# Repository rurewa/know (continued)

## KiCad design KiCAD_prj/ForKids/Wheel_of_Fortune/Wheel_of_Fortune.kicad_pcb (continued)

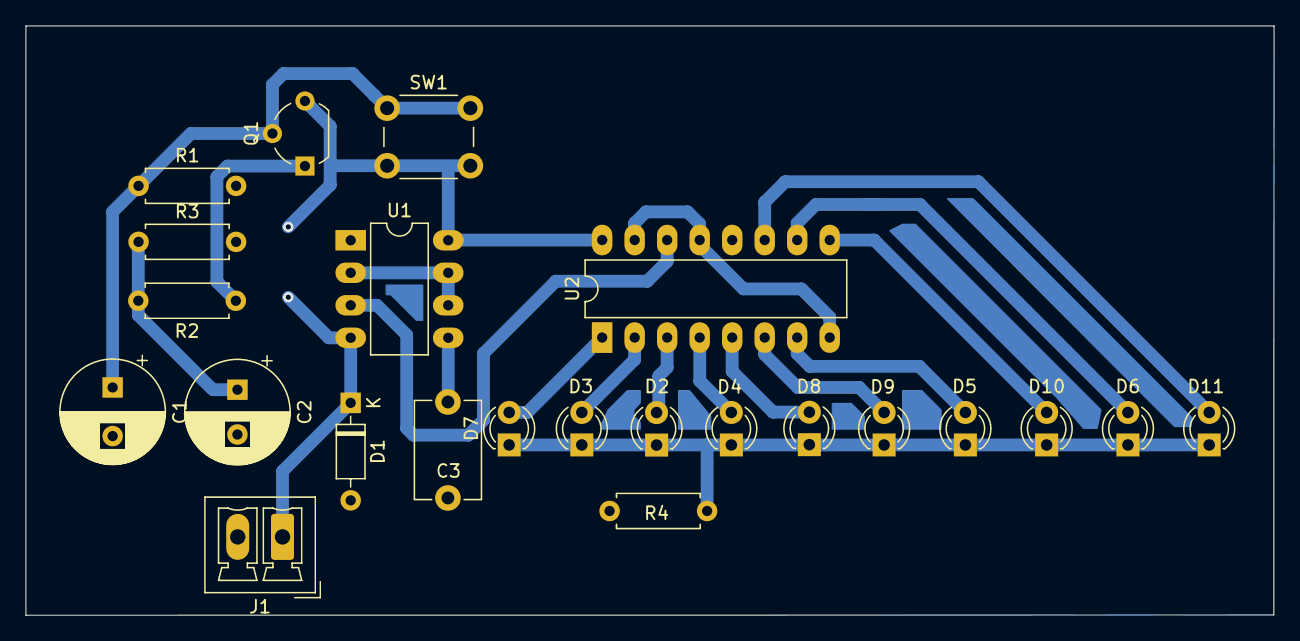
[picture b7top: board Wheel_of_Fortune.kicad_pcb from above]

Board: 2 copper layers, 97.5 x 46.0 mm, 23 parts (0 on the bottom side), 19 nets.

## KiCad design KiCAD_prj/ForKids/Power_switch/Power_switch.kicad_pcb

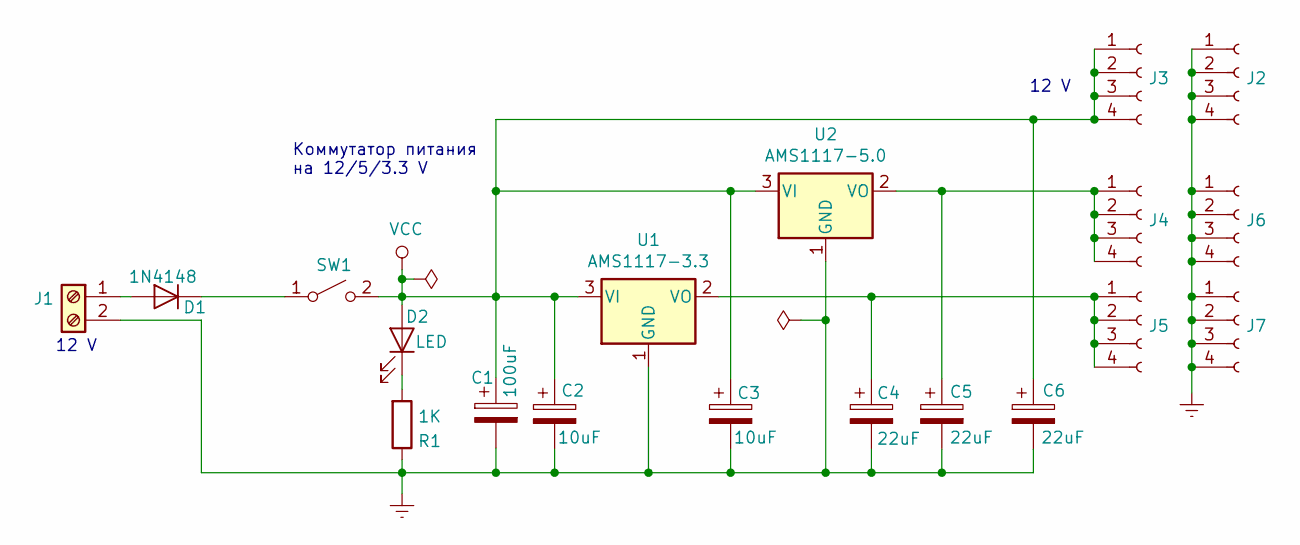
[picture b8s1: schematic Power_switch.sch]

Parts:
C1: 100uF; CP_Radial_D8.0mm_P5.00mm
C2, C3: 10uF; CP_Radial_D5.0mm_P2.50mm
C4, C5, C6: 22uF; CP_Radial_D5.0mm_P2.50mm
D1: 1N4148; D_DO-35_SOD27_P7.62mm_Horizontal
D2: LED; LED_D3.0mm
J1: Screw_Terminal_01x02; PhoenixContact_MCV_1,5_2-G-3.5_1x02_P3.50mm_Vertical
J2, J3, J4, J5, J6, J7: Conn_01x04_Female; PinHeader_1x04_P2.54mm_Vertical
R1: 1K; R_Axial_DIN0207_L6.3mm_D2.5mm_P7.62mm_Horizontal
SW1: SW_SPST; Nidec_Copal_SH-7010C
U1: AMS1117-3.3; SOT-223-3_TabPin2
U2: AMS1117-5.0; SOT-223-3_TabPin2

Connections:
Earth: C1.2, C2.2, C3.2, C4.2, C5.2, C6.2, J1.2, J2.1, J2.2, J2.3, J2.4, J6.1, J6.2, J6.3, J6.4, J7.1, J7.2, J7.3, J7.4, R1.1, U1.1 (GND), U2.1 (GND)
unnamed: C4.1, J5.1, J5.2, J5.3, J5.4, U1.2 (VO)
unnamed: C5.1, J4.1, J4.2, J4.3, J4.4, U2.2 (VO)
unnamed: D1.1 (K), SW1.1 (A)
unnamed: D1.2 (A), J1.1
unnamed: D2.1 (K), R1.2
VCC: C1.1, C2.1, C3.1, C6.1, D2.2 (A), J3.1, J3.2, J3.3, J3.4, SW1.2 (B), U1.3 (VI), U2.3 (VI)

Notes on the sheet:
12 V
Коммутатор питания на 12/5/3.3 V

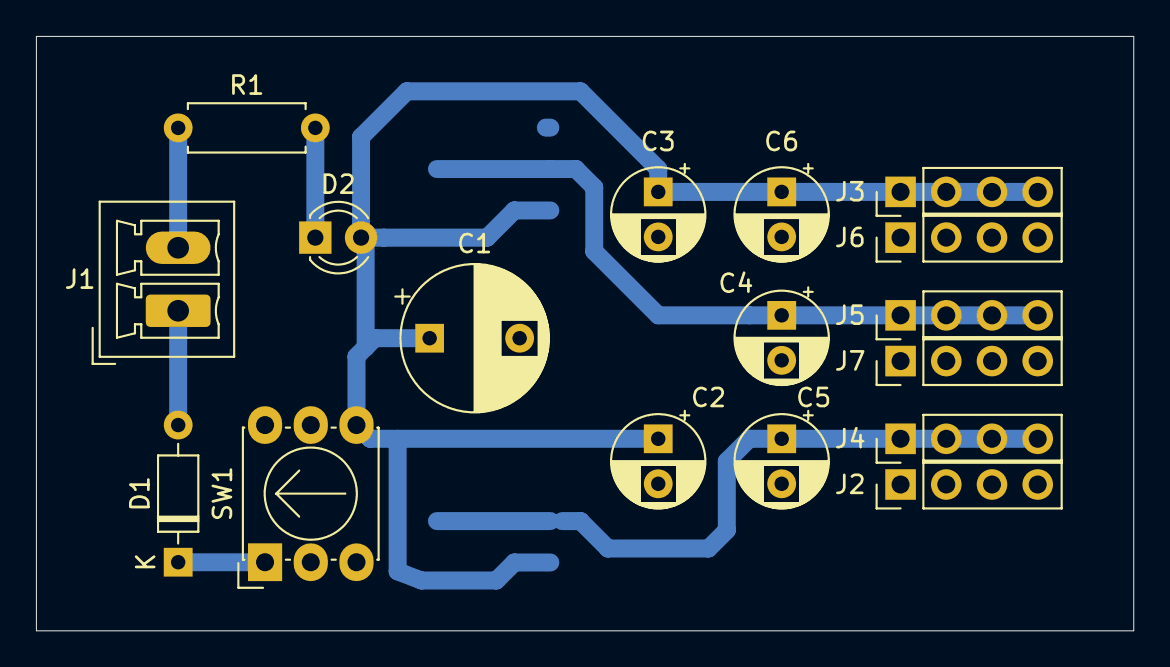
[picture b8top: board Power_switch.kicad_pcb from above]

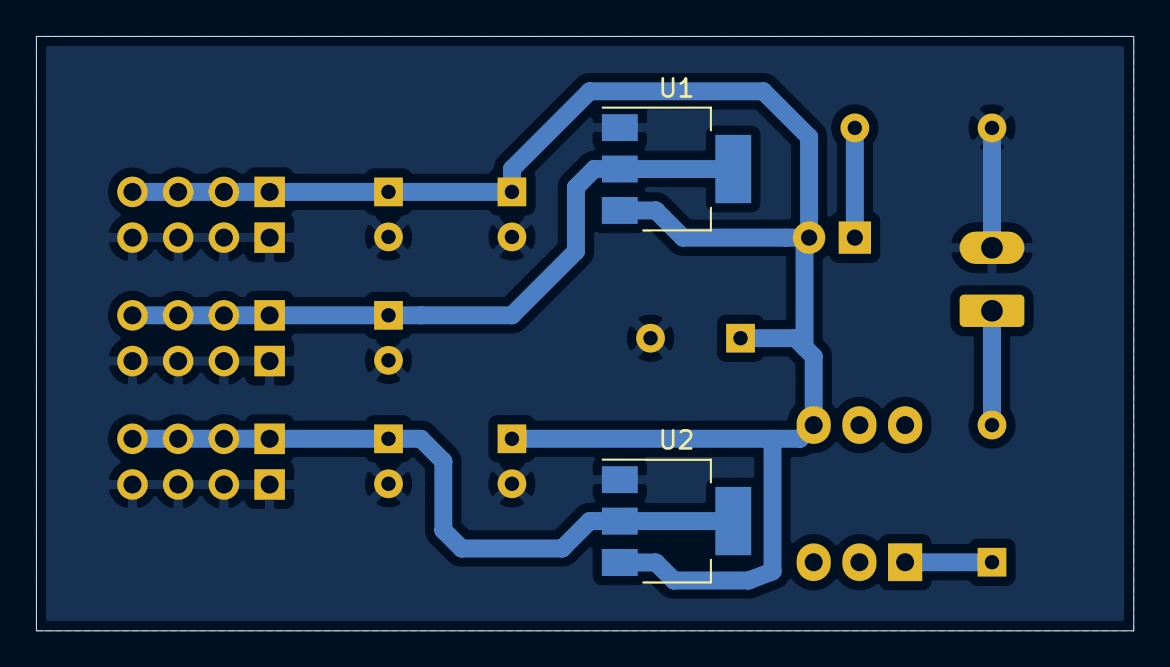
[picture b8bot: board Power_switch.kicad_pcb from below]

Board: 2 copper layers, 61.0 x 33.0 mm, 19 parts (2 on the bottom side), 7 nets.

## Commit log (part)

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2019-03-26 Add comments CARrobo biathlon China Keyes 298
2019-03-31 Rename Random_blink_1 & blink_2 files
2019-04-02 Add Meccanoid smart servo
2019-04-03 Update Sonar track Avoid_Obstacles
2019-04-03 Add TreeIRObstacleDetectors
2019-04-03 Moving file
2019-04-07 Update ThreeIRObstacleDetection add func
2019-04-08 Update Nano_motors_Black_line add function & code optimization
2019-04-12 Update CARrobo_Keyes298_biathlon_frim_China2
2019-04-16 Add sketch NanoMotors from Timothy
2019-04-16 Rename files
2019-04-25 Rename files cpp
2019-04-25 leds switch ... case
2019-04-26 Rename all files .cpp
2019-04-26 Update Leds switch case
2019-04-30 Update Meccanoid add rgb led Eyes
2019-04-30 Add may course
2019-05-11 Add c++ info
2019-05-12 Update sketch a parrot
2019-05-13 Update sketch Led_PWM_potentiometer
2019-05-13 Add sketch Led_PWM_potentiometer_simply
2019-05-16 Update Car Labirint Tim Keyes298
2019-05-16 Update TX BT Keyes298 console
2019-05-19 Add 1 lesson Arduino C++
2019-05-20 Add KiCAD prj NPN miltivibration
2019-05-24 Update Arduino information 1 lesson
2019-05-24 Update comments
2019-05-26 Add mus555 files
2019-05-28 Add Linux information files
2019-06-03 Add and delete Linux information files
2019-06-15 Update files KiCAD mus555 zip
2019-06-19 Tap files Arduino Dev Boards 2.0
2019-06-26 Add sketch RGB button set
2019-06-26 Update sketch RGB switch case set
2019-07-01 Add RGB switch case set for Arduino Dev Board
2019-07-02 Add lessons 4
2019-07-02 02/07/2019
2019-07-04 Add sketch RGB switch case usb 2
2019-07-07 Add Program "Sports of Robototechnix"
2019-07-07 Update 12_algoritm lesson
2019-07-07 Add book Amperka
2019-07-08 Add book Skvoren
2019-07-08 Update lesson Algoritms (12)
2019-07-08 Add books for programming
2019-07-09 Add sketch RGB if switch case one button set end delete pdf file
2019-07-12 Add files project balancing robot
2019-07-12 Add book programming
2019-07-13 Add sketch counter increment one button
2019-07-13 Rename RGB_if_switch_case_button_set.cpp to RGB_counter_if_switch_case_button_set.cpp
2019-07-13 Add to lessons schemes tech
2019-07-15 Add example sketch 7219 led matrix
2019-07-16 Add sketch example flags end picture 8x8 led matrix 7219
2019-07-17 Update sketch example flag 2
2019-07-17 Update 2 sketch example 2
2019-07-17 Update sketch lesson example flag 2
2019-07-19 Add servo bag robot #1
2019-07-19 Many changes
2019-07-19 Move end add files debounce robodem 1
2019-07-19 Update sketch Debounce robodem 1
2019-07-19 Add sketch Debounse Robodem 3
2019-07-20 Add programming files
2019-07-20 Add arduino notebook
2019-07-20 Add sketch Keyes key 5 buttons
2019-07-21 Add book to programming Prata C++
2019-07-21 Update Keyes 5 buttons 2
2019-07-22 Add ArduinoDevBoard files and book C++
2019-07-23 Update Arduino Dev Board
2019-07-23 Add book Sitharta Rao C++
2019-07-25 Add book RAO C++ djvu format end update sketch example flag 2
    A
2019-07-28 Add project Power Switch for Kids
2019-07-29 Update sketch WritingToArrayElements
2019-07-29 Add ASCII table
2019-07-29 Add sketch ArrayLedsMatrixRand
2019-07-30 Add sketch Writing To Array Elements Protection
2019-07-30 Add sketch Declaring Initializing multidimensional Arrays
2019-07-30 Update cpp pdf file
2019-07-31 Add and moving sketch
2019-07-31 Add files carton robots project
2019-08-02 Move folder links
2019-08-06 Add and update KiCad projects
2019-08-06 Add 3D image for Wheel of Fortune project
2019-08-08 Add and update sketch Serial
2019-08-08 Add sketch WaterBot
2019-08-12 Add .png file Grad
2019-08-14 Add algoritm lessoon pdf
2019-08-17 Update and add book Svoren
2019-08-28 Update cpp.pdf and add Program
2019-08-30 Add Hand Bot sketch
2019-09-04 Update progarm
2019-09-08 Rename file
2019-09-08 Add files comp
2019-09-11 Add bases Schem for kids
2019-09-12 Update sketch HandBot
2019-09-12 Add files project HandBot
2019-09-12 Update project HandBot
2019-09-16 Add lesson leds wave pdf file
2019-09-20 To add a file buttons control
2019-09-24 Rename files Button Simple
2019-10-07 Add pdf file WS
2019-10-10 Add boolean .pdf lesson
2019-10-11 Add arduino project SmartBin
2019-11-29 Add picture in Kirill
2019-11-29 Update sketch Kirill project
2019-12-21 Add project ArduinoDevBoard 2.0 in KiCAD
2019-12-22 Update ArduinoDevBoard 2.0 in KiCad
2019-12-22 Add output file .pdf in Arduino Dev Board 2.0
2019-12-23 Update ArduinoDevBoard 2.1 pcb
2020-02-02 Add file sch Arduino Mega
2020-02-20 Add temporary files
2020-02-23 Update end remove files lessons Arduino
2020-03-01 Update files button_contfol and ledsWawe
2020-03-01 Rename file ledsWave.pdf
2020-03-02 Update file Prilohenie
2020-03-06 Update lesson ledWave
2020-03-10 Addd program for ArduiniDevBoard 2.0 leds group wave
2020-03-11 Add file for Provate Folder
2020-03-12 Update program Leds Group One Wave
2020-03-12 Remove files Jun
2020-03-13 Add Morse programm
2020-04-05 Update introductory lesson .pdf file
2020-10-03 Add footprints for KiCad
2020-10-06 Update project Hand Bot. V 1.2/ Added lib end example
2020-10-07 Added robo car bialhlon for Egor D
    Added robo car bialhlon for Egor D
2020-10-08 Added Submarine project by Philipp
2020-10-08 Update Egor car biathllon code
2020-10-08 Deleted file car robot Rgor D
2020-10-08 Egor robot
2020-10-08 Added files for Egor robot
2020-10-09 Added and update files for project Egor/Ilia
2020-10-09 Update code SmartBin
2020-10-09 Update file EgorD end Ilia projects
2020-10-12 Added leds group for pot
2020-10-13 Update program Group Leds For Pot
2020-10-14 Added project for child - bases 1
2020-10-14 Added child project bases 2
2020-10-14 Update Child bases 2 project
2020-10-15 Update Group Leds For Pot
2020-10-16 Update Child bases 2 KiCad project
2020-10-22 Added Car Kegel Ring project
2020-10-30 Update child_babes_2
2020-11-02 Added Power Switch One Row
2020-11-02 Update robot Egor D. project and update Hand Bot man project
2020-11-02 Update Led Control whitch Pot project
2020-11-02 Update RGB Switch Case Set Night Light project
2020-11-05 Rerame and moveng file Arduino Dev Board 2.0 project
2020-11-05 Added Child babes 3 project
2020-11-06 Update Egor D. CarRobot project
2020-11-07 Added Smart Uno Rich Lite project
2020-11-08 Restore know
2020-11-08 Added Open Smart Rich UNO R3
2020-11-10 Add IskraJS projects
2020-11-10 Added sketchs
2020-11-12 Update pdf for Child Babes 2 project
2020-11-13 Update KiCad child bases 2 project
2020-11-13 Added MaxS roboCar project
2020-11-16 Update Arduino information
2020-11-16 Add Cleaner end LineBlackSensor projects
2020-11-17 Added .gitignore
2020-11-17 Added Biathlon sketch
2020-11-17 Add comments to Biathlon sketch
2020-11-18 Added Simply Servo example
2020-11-18 Fix to projects
2020-11-18 Added Stuck Bot
2020-11-19 Update Egors robot car KegelRingSymply
2020-11-19 Update Open Smart Rich Shield - new passive buzzer
2020-11-20 Update Egor robot car KegelRing
2020-11-21 Update Power switch project
2020-11-22 Update OpenSmartRuchShield project
2020-11-23 Add project VSCode for Uno Rish R3
2020-11-24 Update Led Driver RGB project
2020-11-24 Update Led Driver RGB project: fix sintax
2020-11-25 Added Sergy Il. RoboCar sport
2020-11-25 Update .dia for Egors RoboCar, KegelRing
2020-11-25 Added pdf file to Egors RoboCar KegelRing project
2020-11-26 Update pdf output file for Egors CarRotot project
2020-11-29 Added UltraViolet project
2020-12-09 Update Ultraviolet KiCad project
2020-12-09 Added ac/dc converter KiCad project
2020-12-16 Update AC_DC_Converter chem
2020-12-16 Add .pdf file to Child babes 2 project
2020-12-16 Added .pdf file to NanoMotors project
2020-12-16 Add .gitignore file
2020-12-23 added ex1 KiCAD project
2020-12-28 Added to Arduino Dev Board V2 motor, ds18b20 modules
2020-12-29 Added Greenhouse project
2020-12-29 Added Fritzing parts folder
2020-12-29 Update GreenHouse project: added components
2020-12-30 Update GreenHouse project
2021-01-15 Update Egor robot cars: KegelRingSypmle
2021-01-20 Update Arduino Dev Board 2.0 KiCAD project: A6 -> sens t. D2 - free
2021-01-20 Update Egor Robo Cars KegelRingSimply
2021-01-21 Added Ilia project for KegekRing
2021-01-22 Added additional Information for RoboCar KegelRing
2021-01-22 Update Egor cars KegelRingSeple: added black line traking back
2021-01-22 Update Egors robo-cars KegelRingSimply: fix speed for turn and move track
2021-01-22 Update Egors car KegelRingSimply: fixes
2021-01-24 Update Egors roboCar KegelRingSimply
2021-01-26 Update ArduinoDevBoard 2.1 project
2021-01-28 Create .pdf output file from AdruinoDevBoard 2.1 end create folder PlanetaryScientist project
2021-01-28 Update Egors SportCarRobot KegelRing simply project
2021-01-30 Update Egors RoboCasr KegelRingSimoly end pdf file to NanoMotors project
2021-02-03 Update NanoMotors project
2021-02-03 Update ADB 2.1 end NanoMotors projects
2021-02-08 Added SwitchCaseIf to Arduino project
2021-02-09 Added SwitchCaseIf_2 project
2021-02-14 Update Egor robots KegelRingSimply
2021-02-16 Update workspace OpenSmartRichShield project
2021-02-17 Update HandBot project
2021-02-17 Update Child bases2 project
2021-02-19 Update ArduinoDevBoard 2: ad .pdf file. Rename title to schem
2021-02-19 Add info to handBot.odt
2021-02-19 Added file Planetary Scientist project
2021-02-21 Update PlanetaryScientist: update text end fritzing sketch
2021-02-21 Update text to HandBot project
2021-02-21 Update text & .fzz files HandBot project
2021-02-24 Update HandBot doc project
2021-02-25 Update & added files HandBot project
2021-02-25 Update & added files PlanetaryScientist project
2021-02-26 Added krimea project
2021-02-26 Added pitches.h file to OpenSmartRichUnoR3 project
2021-03-01 Added ButtonSeitchCase project
2021-03-01 Added kk
2021-03-03 Fix ArduinoDevBoard 2.0 project: add resistor 100 R to knob
2021-03-05 Update NanoMotors program project: added function end comments
2021-03-05 Fix NanoMotors KiCAD project
2021-03-05 Update NanoMotors project: fix pcd board and update schem pdf file
2021-03-09 Update AllTests for ArduinoDevBoard project: fix comments 8x8 func matrix, add func RGB led test
2021-03-10 Added Symbols potenciometer remote wave to LCD1602 project
2021-03-12 Added i_rob project: robocar from Iliy Let
2021-03-16 Update Child_bases_2 peoject: fix 7 part
2021-03-16 Update Child_bases_2 peoject: fix 7 part end update pdf file
2021-03-17 Add git book
2021-03-17 Added English_Russian dictionary_IT.pdf
2021-03-18 Update EgorDor KegelRingSymple robot car
2021-03-19 Update Egors roboCar KegelRingSymple 1: fix speed move
2021-03-19 Update Egors roboCar KegelRingSymple 1: fix speed move and false wath pins"
2021-03-31 Update EgorDor KegelRingSymple project
2021-04-02 Added Rocket Control project
2021-04-02 Added gif
2021-04-05 Added Counter two button project
2021-04-05 Deleted
2021-04-06 Update Counter two button project
2021-04-07 Update Egor robotCar KegelRingSymple V 1.6 project
2021-04-07 Update Egor robotCar KegelRingSymple V 1.7 project
2021-04-08 Added Leds Buttom Two Control Whitch Count Limit project for ADB 2
2021-04-08 Restore AllTests.cpp for ADB 2
2021-04-09 LedsButtomTwoControlWhitchCountLimit
2021-04-09 Update EgorDor KegelRingSymple 12V
2021-04-09 Added EgorDor KegelRingSymple7_4V project
2021-04-13 Added Pedagogy and Education magazine
2021-04-15 Update Egor roboCAR KegelRingSymply 12V
2021-04-15 Update child bases 2
2021-04-16 Fix LedsButtomTwoControlWhitchCountLimit project: > limit
2021-04-20 Update MenuLCDdisplyThreeButtons project
2021-04-20 Update MenuLCDdisplyThreeButtons project: added functions
2021-04-20 Fix child_bases_2 projectL: remove numbers a task
2021-04-21 Update BiathlonSimply_20mm_12V to Egor RoboCar project
2021-04-23 Fix: added sensors.begin() MenuLCDdisplyThreeButtons project
2021-04-26 Added example project for my book
2021-05-14 Added InfraredControl
2021-05-18 Update InfraredControl.ino Dima S.
2021-05-19 Update AllTests.cpp: add complex expression
2021-05-19 Added pot_control.ino
2021-05-22 Added GIT lesson project
2021-05-25 Added libry ot Fritzing parts
2021-05-25 Added exampleSimplyLogicalOperations.ino: simply logical operations
2021-05-27 Add pins for Open_Smart_Rich_UNO_R3 project
2021-06-04 Added ch340g datasheet
2021-07-04 Add RF433 project
2021-07-08 Add NRF24L01 Tanl_2WD project
